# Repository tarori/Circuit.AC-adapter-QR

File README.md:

Quasi-resonant AC adapter
 * AC100V to ±20V 2A
 * Use STR-Y6735

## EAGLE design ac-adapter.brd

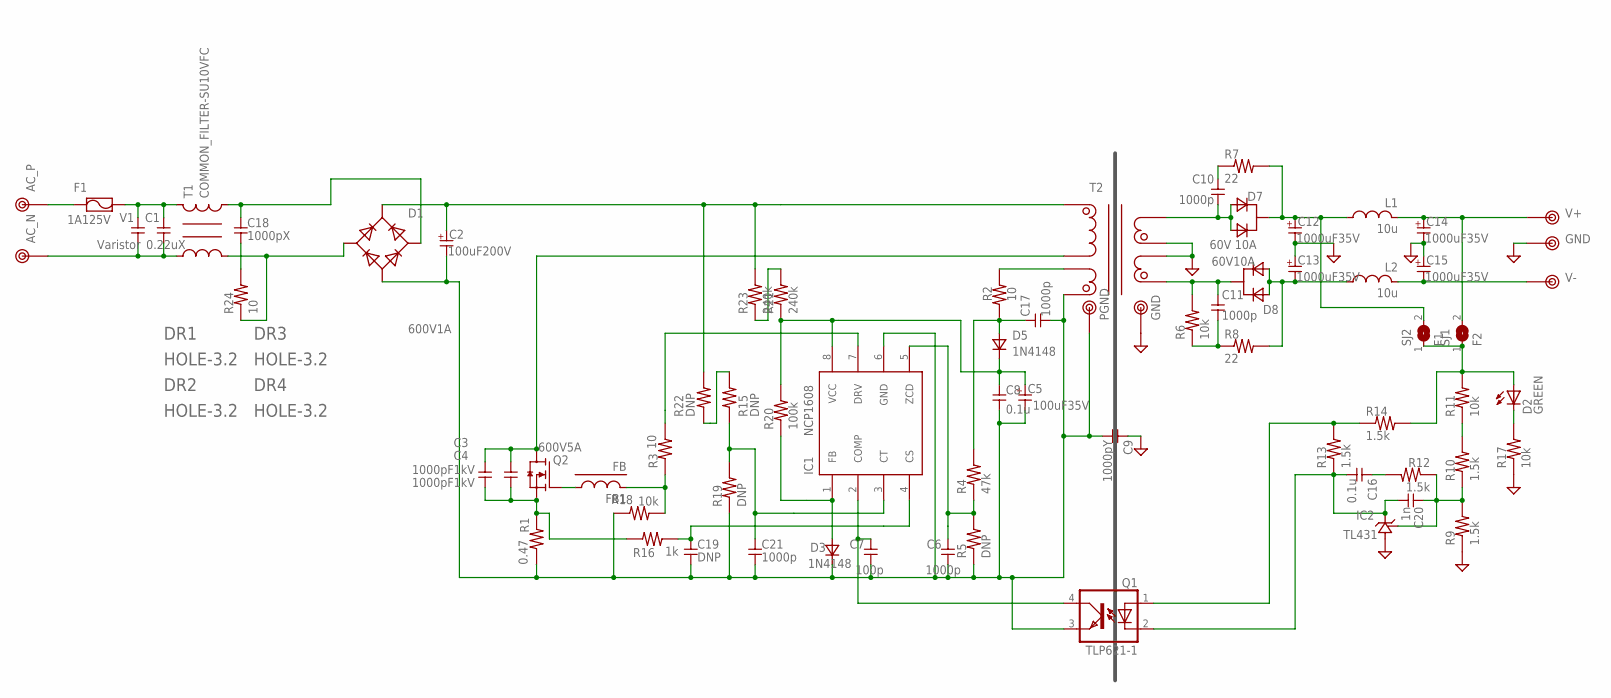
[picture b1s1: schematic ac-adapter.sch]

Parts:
C1: 0.22uX; X-CAPACITER
C2: 100uF200V; E5-16A2
C3, C4: 1000pF1kV; C050
C5: 100uF35V; E2,5-8
C6, C10, C11, C17, C21: 1000p; 1608
C7: 100p; 1608
C8: 0.1u; 2012
C9: 1000pY; Y-CAPACITER
C12, C13: 1000uF35V; E5-13
C14, C15: 1000uF35V; E5-10
C16: 0.1u; 1608
C18: 1000pX; C050
C19: DNP; 1608
C20: 1n; 1608
D1: 600V1A; GBU8A
D2: GREEN; D1608
D3, D5: 1N4148; SOD123
D7: 60V 10A; TO-220
D8: 60V10A; TO-220
DR1, DR2, DR3, DR4: HOLE-3.2; HOLE_3.2
F1: 1A125V; FUSE-5
FB1: FB; 1608-FB
IC1: NCP1608; SOP8
IC2: TL431; TO-92
L1, L2: 10u; L5-7,5
Q1: TLP621-1; DIL04
Q2: 600V5A; PQFN8X8
R1: 0.47; 0207/10
R2, R3, R24: 10; 2012
R4: 47k; 1608
R5, R15, R19, R22: DNP; 1608
R6, R11, R17, R18: 10k; 1608
R7, R8: 22; 2012
R9, R10, R12, R13, R14: 1.5k; 1608
R16: 1k; 1608
R20: 100k; 1608
R21, R23: 240k; 1608
SJ1: F2; 1608-J
SJ2: F1; 1608-J
T1: COMMON_FILTER-SU10VFC; SU10VFC
T2: TRANSFORMAER_FLYBACK-PQ2620-2; BPQ26/20-1112CPFR
TP1: AC_P; TESTPIN-LARGE
TP2: AC_N; TESTPIN-LARGE
TP3: V+; TESTPIN-LARGE
TP4: GND; TESTPIN-LARGE
TP5: V-; TESTPIN-LARGE
TP6: GND; TESTPIN-BIG
TP7: PGND; TESTPIN-BIG
V1: Varistor; C050

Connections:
GND: C9.1, C12.- (2), C13.+ (1), C14.- (2), C15.+ (1), IC2.2 (GND), R9.1, R17.1, T2.9 (L3_P), T2.10 (L4_N), TP4.1, TP6.1
unnamed: F1.1, TP1.1
unnamed: C1.2, T1.1, TP2.1, V1.2
unnamed: C1.1, F1.2, T1.4, V1.1
unnamed: D1.2 (AC1), R24.1, T1.2
unnamed: C21.1, IC1.3 (CT), R15.1, R19.2
unnamed: C12.+ (1), D7.2 (K), L1.2 (1), R7.2, SJ2.2
unnamed: C6.1, IC1.5 (ZCD), R4.1, R5.2
unnamed: C10.1, R7.1
unnamed: D2.A, R11.2, R14.2, SJ1.1, SJ2.1
unnamed: R2.2, T2.6 (L2_N)
unnamed: C17.1, D5.1 (A), R2.1, R4.2
unnamed: C3.2, C4.2, Q2.S, R1.2, R16.1
unnamed: IC1.7 (DRV), R3.2
unnamed: FB1.2, R3.1, R18.1
unnamed: C19.1, IC1.4 (CS), R16.2
unnamed: C18.1, D1.3 (AC2), T1.3
unnamed: C10.2, D7.1 (A1), D7.3 (A2), T2.7 (L3_N), T2.8 (L3_N)
unnamed: C11.1, D8.2 (K), R6.2, T2.11 (L4_P), T2.12 (L4_P)
unnamed: C7.1, IC1.2 (COMP), Q1.4 (COL)
unnamed: FB1.1, Q2.G
unnamed: D2.K, R17.2
unnamed: C11.2, R6.1, R8.1
unnamed: C13.- (2), D8.1 (A1), D8.3 (A2), L2.2 (1), R8.2
unnamed: D3.1 (A), IC1.1 (FB), R20.1
unnamed: R10.2, R11.1
unnamed: C20.1, IC2.1 (REF), R9.2, R10.1, R12.1
unnamed: C16.1, R12.2
unnamed: C16.2, C20.2, IC2.3 (OUT), Q1.2 (C), R13.1
unnamed: Q1.1 (A), R13.2, R14.1
unnamed: R15.2, R22.1
unnamed: R21.2, R23.1
unnamed: C18.2, R24.2
PGND: C2.- (2), C5.- (2), C6.2, C7.2, C8.2, C9.2, C17.2, C19.2, C21.2, D1.4 (V-), D3.2 (K), IC1.6 (GND), Q1.3 (EMIT), R1.1, R5.1, R18.2, R19.1, T2.5 (L2_P), TP7.1
SW: C3.1, C4.1, Q2.D, T2.1 (L1_N)
V+: C14.+ (1), L1.1 (2), SJ1.2, TP3.1
V-: C15.- (2), L2.1 (2), TP5.1
VCC: C5.+ (1), C8.1, D5.2 (K), IC1.8 (VCC), R20.2, R21.1
VP: C2.+ (1), D1.1 (V+), R22.2, R23.2, T2.3 (L1_P)

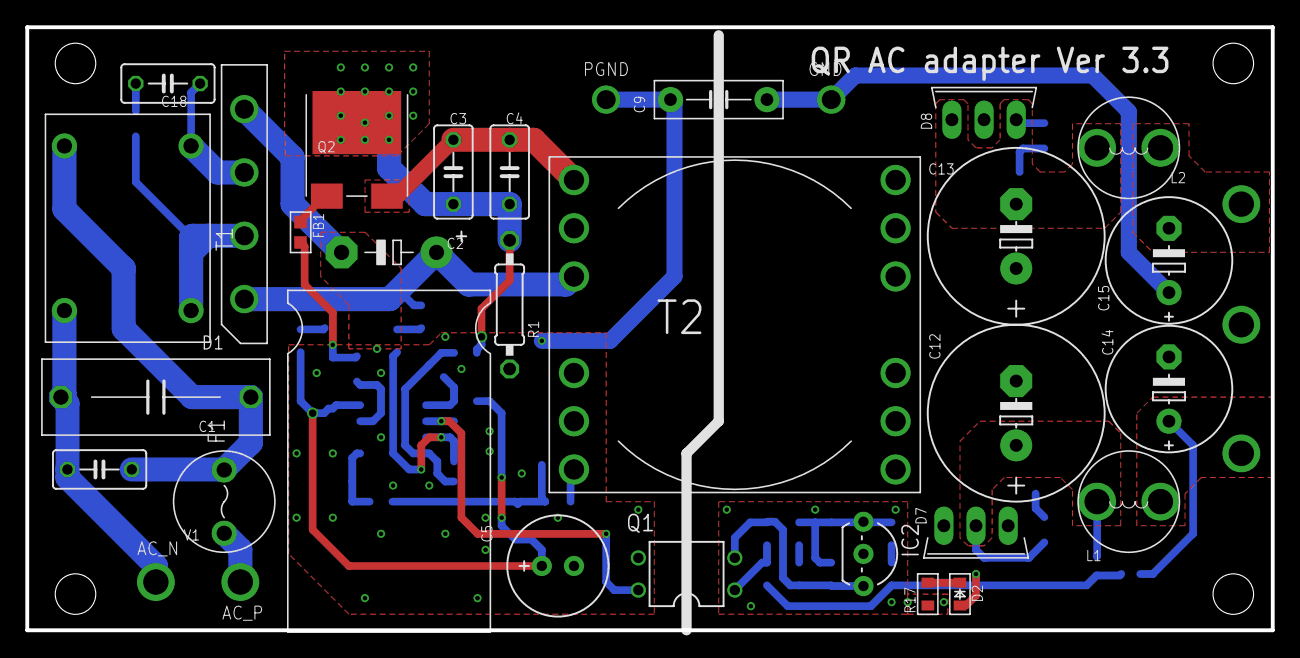
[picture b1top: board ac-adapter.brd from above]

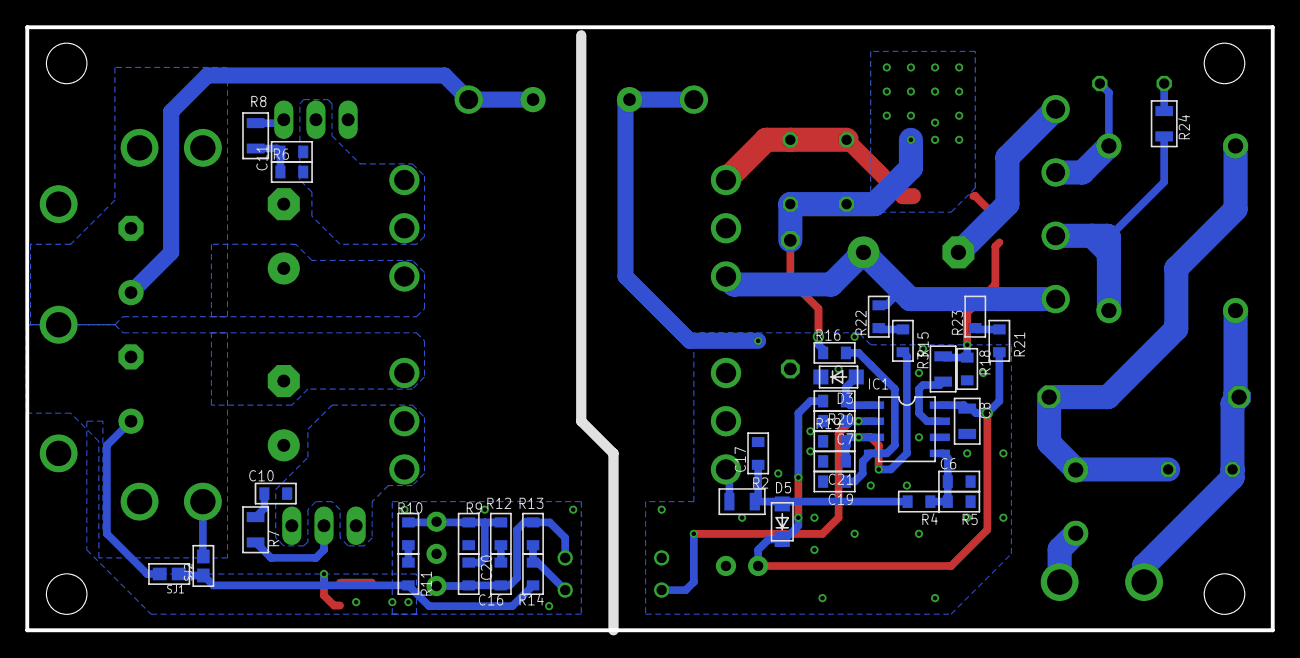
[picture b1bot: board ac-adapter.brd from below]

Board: 2 copper layers, 98.4 x 47.6 mm, 75 parts (37 on the bottom side), 39 nets.

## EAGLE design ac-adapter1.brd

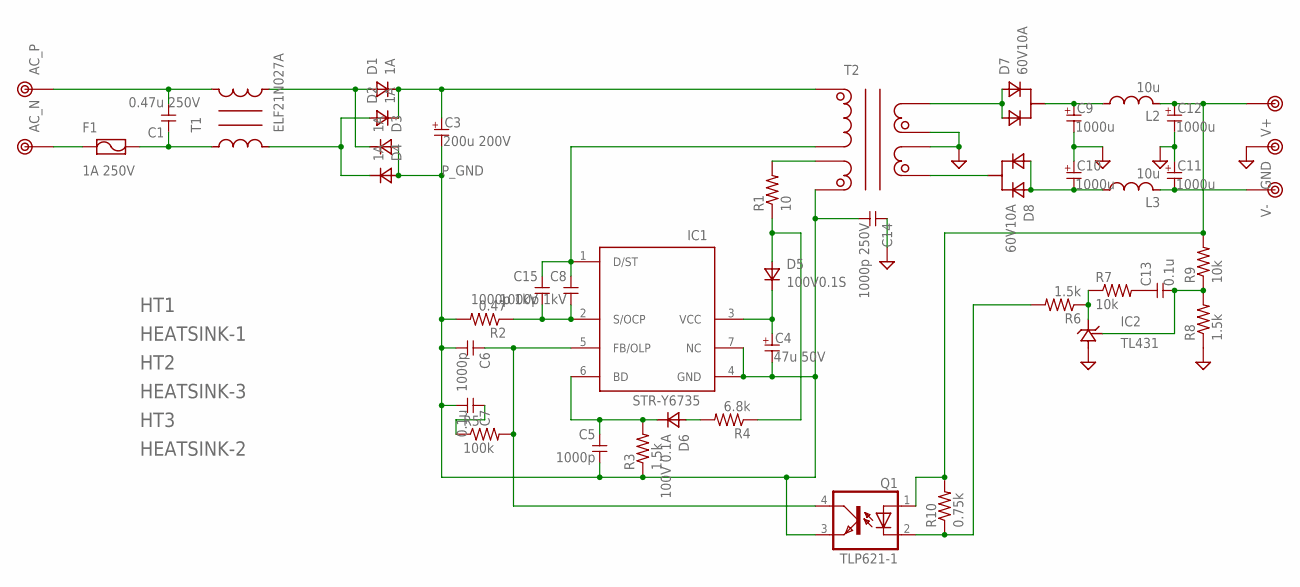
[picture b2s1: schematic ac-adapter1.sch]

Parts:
C1: 0.47u 250V; C050-030X075
C3: 200u 200V; E5-13
C4: 47u 50V; E2.5-6.5
C5, C6: 1000p; 1608
C7, C13: 0.1u; 1608
C8, C15: 1000p 1kV; C050-030X075
C9, C10, C11, C12: 1000u; E2,5-8
C14: 1000p 250V; C050-030X075
D1, D2, D3, D4: 1A; D0204/7
D5: 100V0.1S; D0207/2V
D6: 100V 0.1A; D0207/2V
D7, D8: 60V10A; TO-220
F1: 1A 250V; FUSE_20MM
HT1: HEATSINK-1; HEATSINK1
HT2: HEATSINK-3; HEATSINK3
HT3: HEATSINK-2; HEATSINK2
IC1: STR-Y6735; TO220F-7L-UNIVERSAL
IC2: TL431; TO-92
L2, L3: 10u; L5-7,5
Q1: TLP621-1; DIL04
R1: 10; 0207/10
R2: 0.47; 0207/10
R3, R6, R8: 1.5k; 1608
R4: 6.8k; 0207/2V
R5: 100k; 1608
R7, R9: 10k; 1608
R10: 0.75k; 1608
T1: ELF21N027A
T2: TRANSFORMAER_FLYBACK-PQ3535; BPQ35/35-1112CPFR
TP1: AC_P; TESTPIN
TP2: AC_N; TESTPIN
TP3: V+; TESTPIN
TP4: V-; TESTPIN
TP5: GND; TESTPIN

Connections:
GND: C9.- (2), C10.+ (1), C11.+ (1), C12.- (2), C14.1, IC2.2 (GND), R8.1, T2.9 (L3_P), T2.10 (L4_N), TP5.1
unnamed: F1.1-1, F1.1-2, TP2.1
unnamed: C1.1, F1.2-1, F1.2-2, T1.1
unnamed: C1.2, T1.4, TP1.1
unnamed: D2.1 (A), D4.2 (K), T1.2
unnamed: D7.1 (A1), D7.3 (A2), T2.8 (L3_N)
unnamed: C8.1, C15.1, IC1.1 (D/ST), T2.3 (L1_N)
unnamed: D1.1 (A), D3.2 (K), T1.3
unnamed: C3.+ (1), D1.2 (K), D2.2 (K), T2.1 (L1_P)
unnamed: C4.+ (1), D5.2 (K), IC1.3 (VCC)
unnamed: D5.1 (A), R1.1, R4.1
unnamed: R1.2, T2.5 (L2_N)
unnamed: C8.2, C15.2, IC1.2 (S/OCP), R2.1
unnamed: D6.1 (A), R4.2
unnamed: C5.1, D6.2 (K), IC1.6 (BD), R3.2
unnamed: C6.1, IC1.5 (FB/OLP), Q1.4 (COL), R5.2
unnamed: C7.1, R5.1
unnamed: D8.2 (K), T2.11 (L4_P)
unnamed: C10.- (2), D8.1 (A1), D8.3 (A2), L3.P$1 (1)
unnamed: C9.+ (1), D7.2 (K), L2.P$1 (1)
unnamed: C13.2, IC2.1 (REF), R8.2, R9.1
unnamed: C12.+ (1), L2.P$2 (2), Q1.1 (A), R9.2, R10.2, TP3.1
unnamed: C11.- (2), L3.P$2 (2), TP4.1
unnamed: IC2.3 (OUT), R6.1, R7.1
unnamed: C13.1, R7.2
unnamed: Q1.2 (C), R6.2, R10.1
P_GND: C3.- (2), C4.- (2), C5.2, C6.2, C7.2, C14.2, D3.1 (A), D4.1 (A), IC1.4 (GND), IC1.7 (NC), Q1.3 (EMIT), R2.2, R3.1, T2.4 (L2_P)

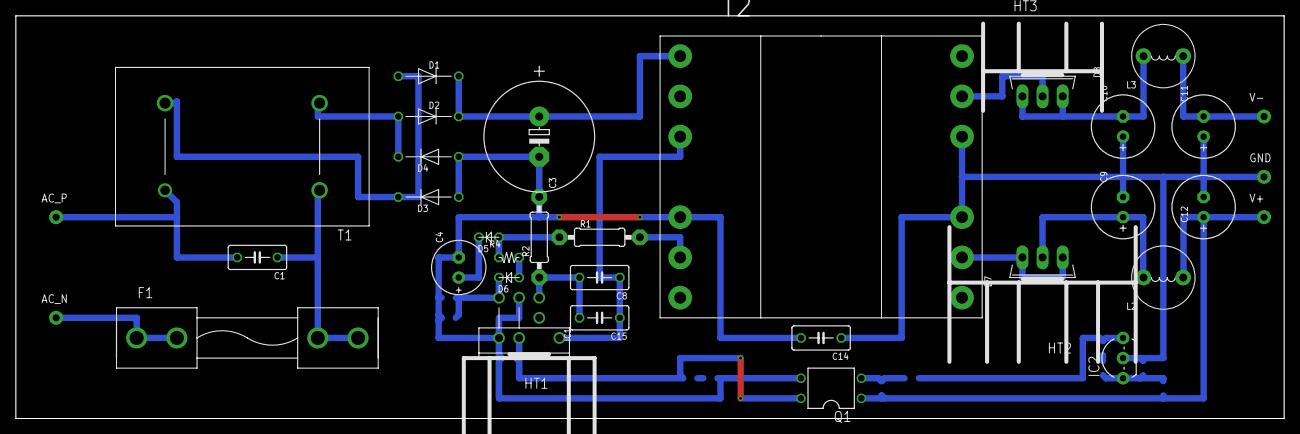
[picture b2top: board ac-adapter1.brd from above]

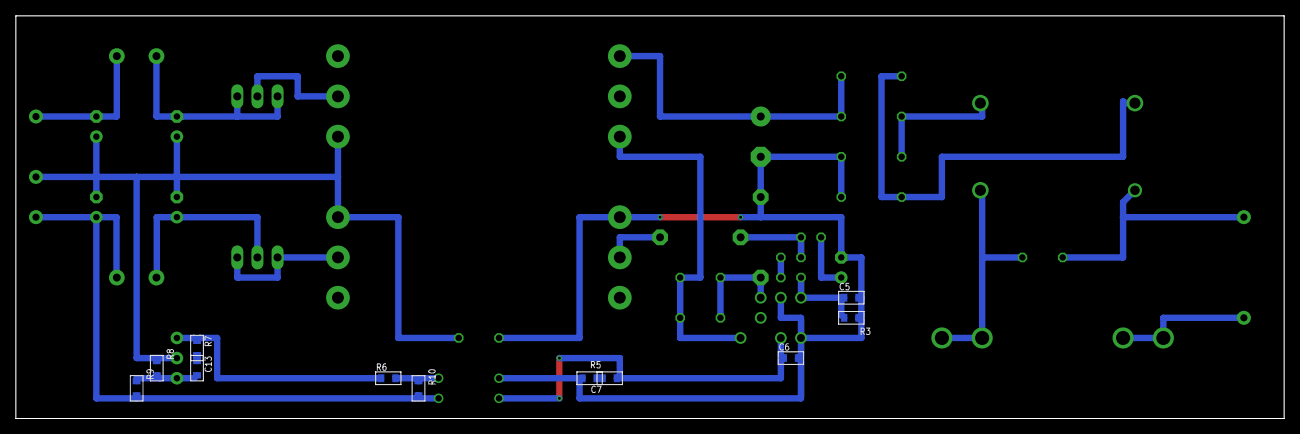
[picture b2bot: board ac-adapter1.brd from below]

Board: 2 copper layers, 160.0 x 50.8 mm, 48 parts (11 on the bottom side), 27 nets.

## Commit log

2020-06-10 Prototype worked
2020-07-12 Add README
2022-04-10 BM1Q011FJを使う
2022-04-14 PGND変更
2022-04-24 tiny
2023-07-29 PFCコントローラーを使う
2023-09-02 パターン修正
2023-11-04 GaNに対応
